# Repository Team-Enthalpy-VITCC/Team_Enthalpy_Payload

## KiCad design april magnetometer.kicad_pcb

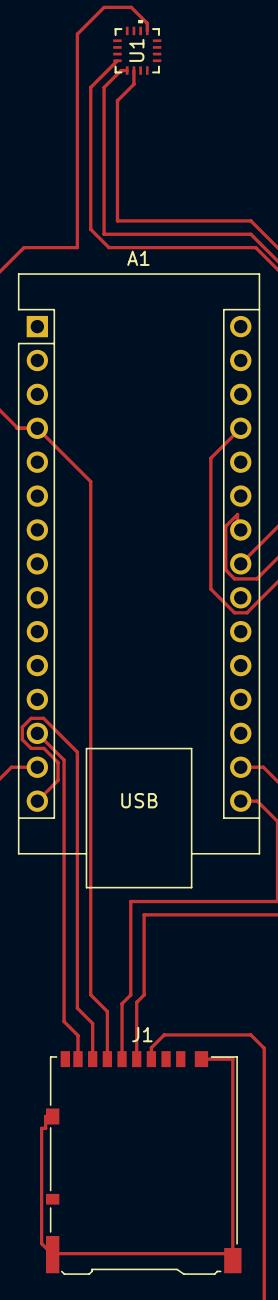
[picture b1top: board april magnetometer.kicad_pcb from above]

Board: 2 copper layers, 3 parts (0 on the bottom side), 9 nets.

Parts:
A1: rduino_Nano_v2.x; Arduino_Nano
J1: Micro_SD_Card_Det2; microSD_HC_Hirose_DM3AT-SF-PEJM5
U1: HMC5883L; LPCC16_HNW

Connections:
unnamed: A1.17 (3V3), J1.4 (VDD)
unnamed: A1.27 (+5V), U1.2 (VDD)
unnamed: A1.23 (A4), U1.16 (SDA)
unnamed: A1.24 (A5), U1.1 (SCL)
unnamed: A1.13 (D10), J1.8 (DAT1)
unnamed: A1.14 (D11), J1.3 (CMD)
unnamed: A1.15 (D12), J1.7 (DAT0)
unnamed: A1.16 (D13), J1.5 (CLK)
unnamed: A1.4 (GND), J1.6 (VSS), U1.9 (GND)

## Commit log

2024-02-19 cubesat resources
2024-03-08 version 1 : previous
2024-03-08 version 2
